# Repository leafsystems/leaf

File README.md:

# Leaf Systems

All code and hardware to launch the Leaf backend, edge devices, IoT devices, etc.

## Cloud

Monolithic ingestion service

- Endpoint for delivering data
- A liveview app written in Dioxus.

Deployed to vercel (????)

## User App

Again, a liveview app written in Dioxus. A bit of a holdover until we deploy a real app.

## ingestion 

Service

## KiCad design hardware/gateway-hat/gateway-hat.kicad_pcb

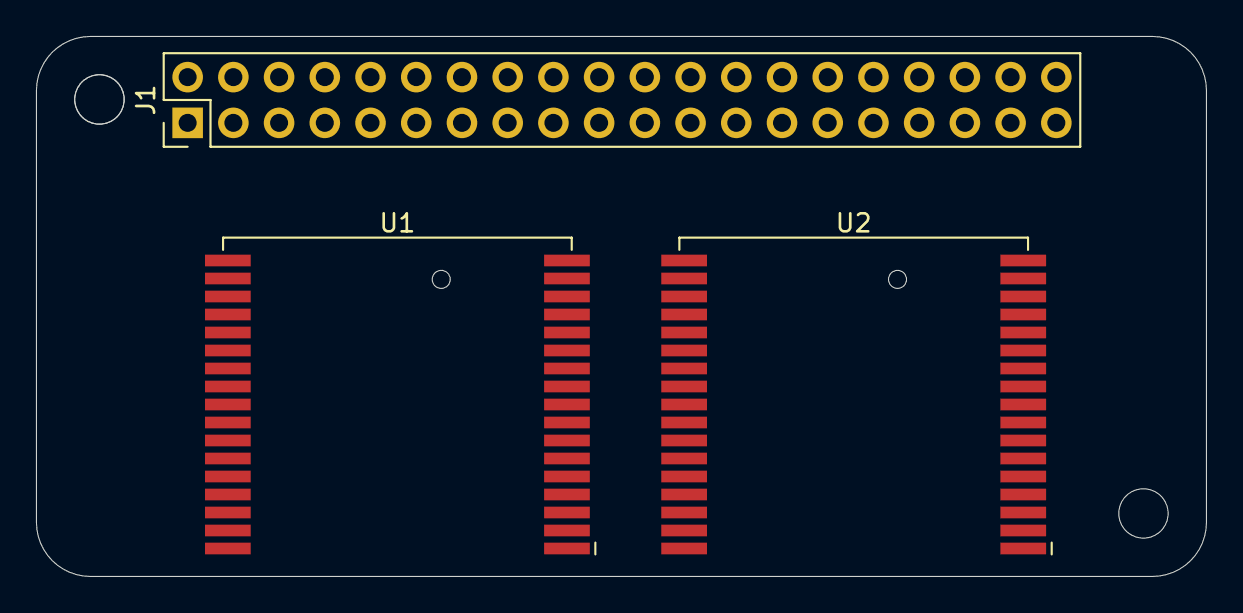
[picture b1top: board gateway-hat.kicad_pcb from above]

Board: 2 copper layers, 65.0 x 30.0 mm, 3 parts (0 on the bottom side), 2 nets, no tracks yet.

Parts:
J1: Conn_02x20_Odd_Even; PinHeader_2x20_P2.54mm_Vertical
U1, U2: DWM1001; DecaWave_DWM1001

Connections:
unnamed: U1.1 (GND), U1.11 (GND), U1.24 (GND), U1.34 (GND)
unnamed: U2.1 (GND), U2.11 (GND), U2.24 (GND), U2.34 (GND)

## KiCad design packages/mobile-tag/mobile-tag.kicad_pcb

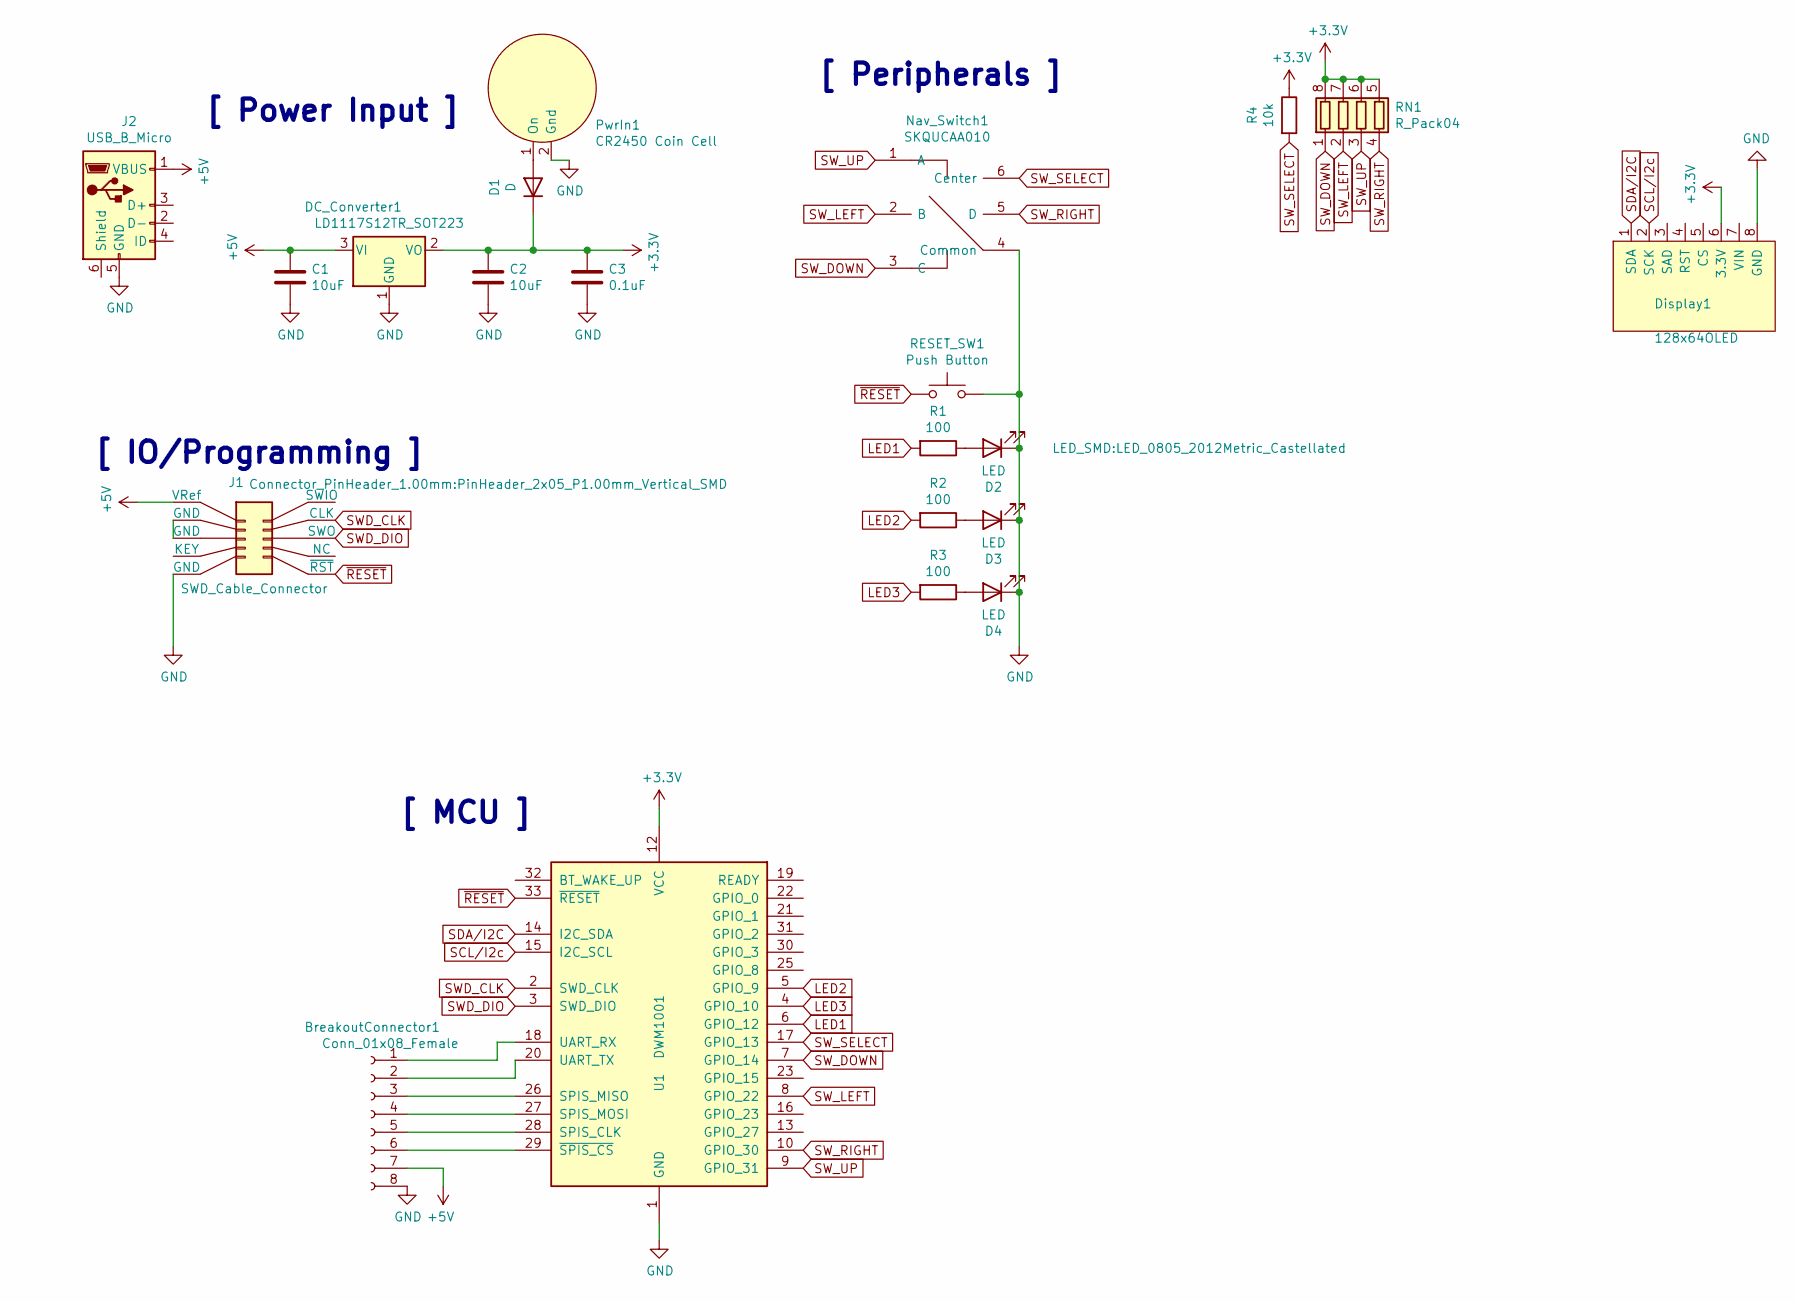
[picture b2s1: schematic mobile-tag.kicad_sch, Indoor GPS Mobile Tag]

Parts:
BreakoutConnector1: Conn_01x08_Female; PinSocket_1x08_P2.54mm_Horizontal
C1: 10uF; C_0805_2012Metric_Pad1.15x1.40mm_HandSolder; JLCPCB C15850
C2: 10uF; C_Radial_D5.0mm_H5.0mm_P2.00mm; JLCPCB C15850
C3: 0.1uF; R_0603_1608Metric_Pad1.05x0.95mm_HandSolder; JLCPCB C49678
D1: D; D_5W_P10.16mm_Horizontal; JLCPCB C22452
D2: LED; LED_0805_2012Metric_Castellated; JLCPCB C34499
D3, D4: LED; LED_D3.0mm; JLCPCB C34499
DC_Converter1: LD1117S12TR_SOT223; SOT-223-3_TabPin2; JLCPCB C116068
Display1: 128x64OLED; Adafruit_SSD1306
J1: SWD_Cable_Connector; PinHeader_2x05_P1.00mm_Vertical_SMD
J2: USB_B_Micro; USB_Micro-B_Wuerth_629105150521
Nav_Switch1: SKQUCAA010; Manufacturer_Part_Number SKQUCAA010; Mouser Part Number 688-SKQUCA
PwrIn1: CR2450 Coin Cell; BatteryHolder_Keystone_3009_1x2450
R1: 100; R_Axial_DIN0204_L3.6mm_D1.6mm_P5.08mm_Vertical; JLCPCB C17901
R2, R3: 100; R_1206_3216Metric_Pad1.42x1.75mm_HandSolder; JLCPCB C17901
R4: 10k; R_1206_3216Metric_Pad1.42x1.75mm_HandSolder; JLCPCB C17902
RESET_SW1: Push Button; SW_PUSH_6mm_H5mm
RN1: R_Pack04; R_Array_Convex_4x0603; JLCPCB C29718
U1: DWM1001; DecaWave_DWM1001

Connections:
GND: BreakoutConnector1.8, C1.2, C2.2, C3.2, D2.1 (K), D3.1 (K), D4.1 (K), DC_Converter1.1 (GND), Display1.8 (GND), J1.9 (GND), J2.5 (GND), Nav_Switch1.4 (Common), PwrIn1.2 (Gnd), RESET_SW1.2, U1.1 (GND), U1.11 (GND), U1.24 (GND), U1.34 (GND)
LED1: R1.2, U1.6 (GPIO_12)
LED2: R2.2, U1.5 (GPIO_9)
LED3: R3.2, U1.4 (GPIO_10)
unnamed: BreakoutConnector1.1, U1.18 (UART_RX)
unnamed: BreakoutConnector1.2, U1.20 (UART_TX)
unnamed: BreakoutConnector1.3, U1.26 (SPIS_MISO)
unnamed: BreakoutConnector1.4, U1.27 (SPIS_MOSI)
unnamed: BreakoutConnector1.5, U1.28 (SPIS_CLK)
unnamed: BreakoutConnector1.6, U1.29 (~SPIS_CS)
unnamed: D1.2 (A), PwrIn1.1 (On)
unnamed: D2.2 (A), R1.1
unnamed: D3.2 (A), R2.1
unnamed: D4.2 (A), R3.1
unnamed: J1.3 (GND), J1.5 (GND)
SCL/I2c: Display1.2 (SCK), U1.15 (I2C_SCL)
SDA/I2C: Display1.1 (SDA), U1.14 (I2C_SDA)
SWD_CLK: J1.4 (CLK), U1.2 (SWD_CLK)
SWD_DIO: J1.6 (SWO), U1.3 (SWD_DIO)
SW_DOWN: Nav_Switch1.3 (C), RN1.1 (R1.1), U1.7 (GPIO_14)
SW_LEFT: Nav_Switch1.2 (B), RN1.2 (R2.1), U1.8 (GPIO_22)
SW_RIGHT: Nav_Switch1.5 (D), RN1.4 (R4.1), U1.10 (GPIO_30)
SW_SELECT: Nav_Switch1.6 (Center), R4.2, U1.17 (GPIO_13)
SW_UP: Nav_Switch1.1 (A), RN1.3 (R3.1), U1.9 (GPIO_31)
~RESET: J1.10 (~RST), RESET_SW1.1, U1.33 (~RESET)

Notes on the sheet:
[ IO/Programming ]
[ Power Input ]
[ MCU ]
[ Peripherals ]

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
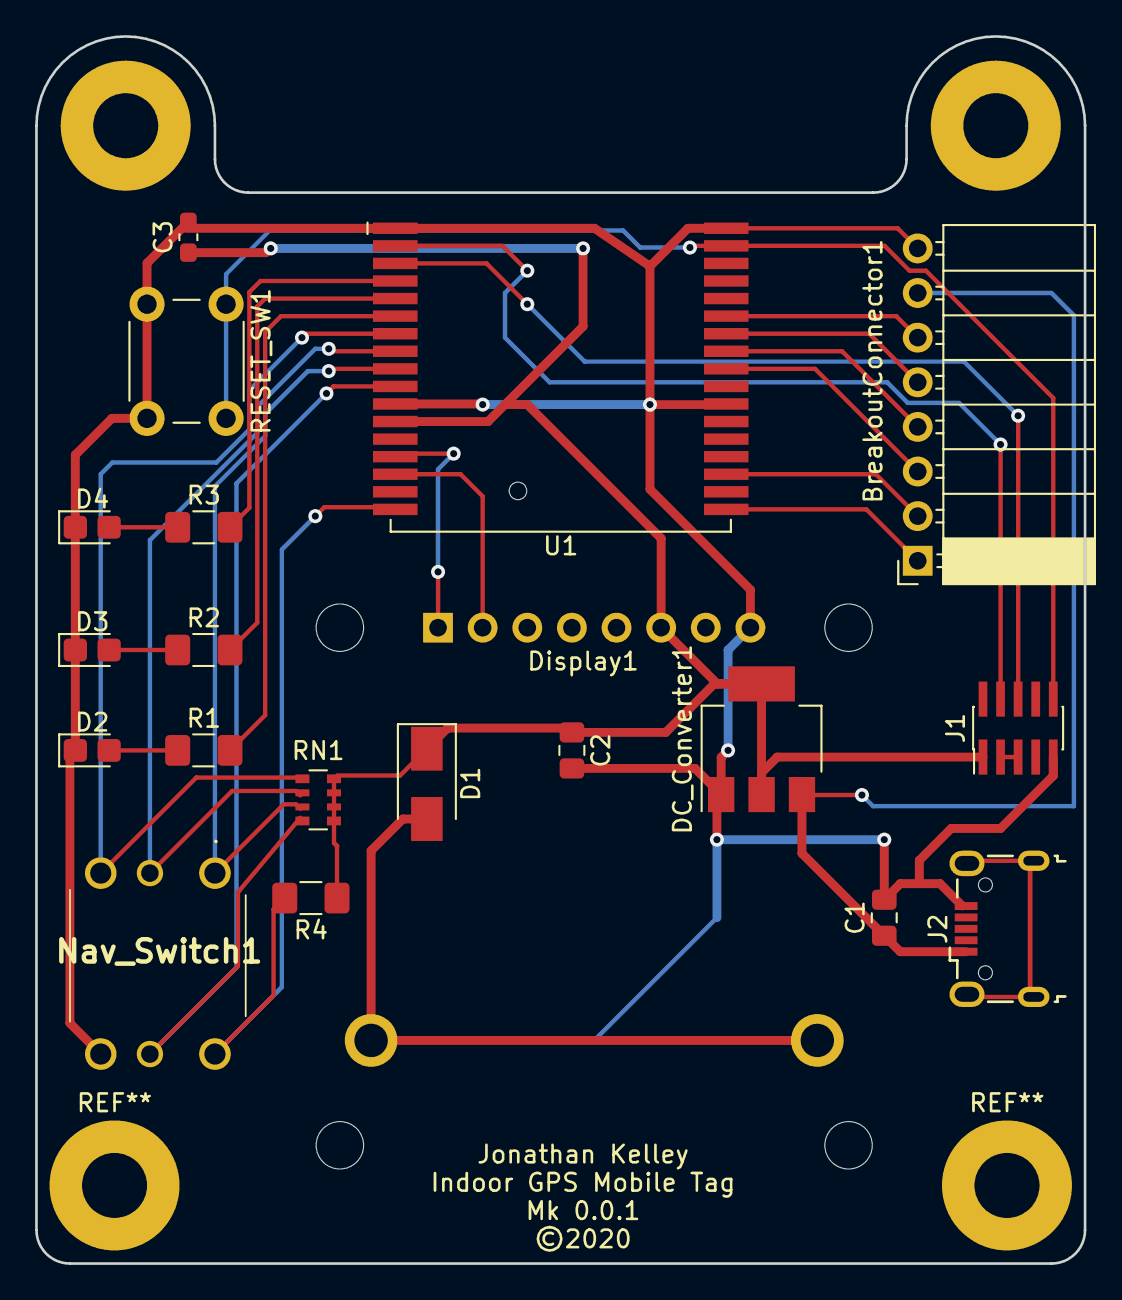
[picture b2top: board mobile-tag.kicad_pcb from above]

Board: 2 copper layers, 59.7 x 69.9 mm, 21 parts (1 on the bottom side), 27 nets.

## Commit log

2020-12-16 Feat: updates all around
2020-12-17 Feat: whole system up and running
2020-12-31 Feat: add site
2022-02-22 wip: move things around
2022-02-22 wip: commit tag code
2022-02-24 wip: real time data logging
2022-03-07 feat: get schema built on and some basic data
2022-03-15 wip: tweak datalog code
2022-03-17 feat: liveview works
2022-03-19 wip: readme
2022-03-31 feat: prettier app
2022-04-06 feat: it's working with single anchor setup
2022-05-04 feat: localization working
2022-05-05 feat: add collected data and refactor localization

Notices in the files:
hardware/gateway-hat/gateway-hat.kicad_pcb:
License: MIT - Copyright 2018 StudioPieters®
packages/mobile-tag/mobile-tag.kicad_pcb:
©2020
